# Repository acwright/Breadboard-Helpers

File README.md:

# Breadboard Helpers

A set of circuit boards to make breadboarding and prototyping easier!

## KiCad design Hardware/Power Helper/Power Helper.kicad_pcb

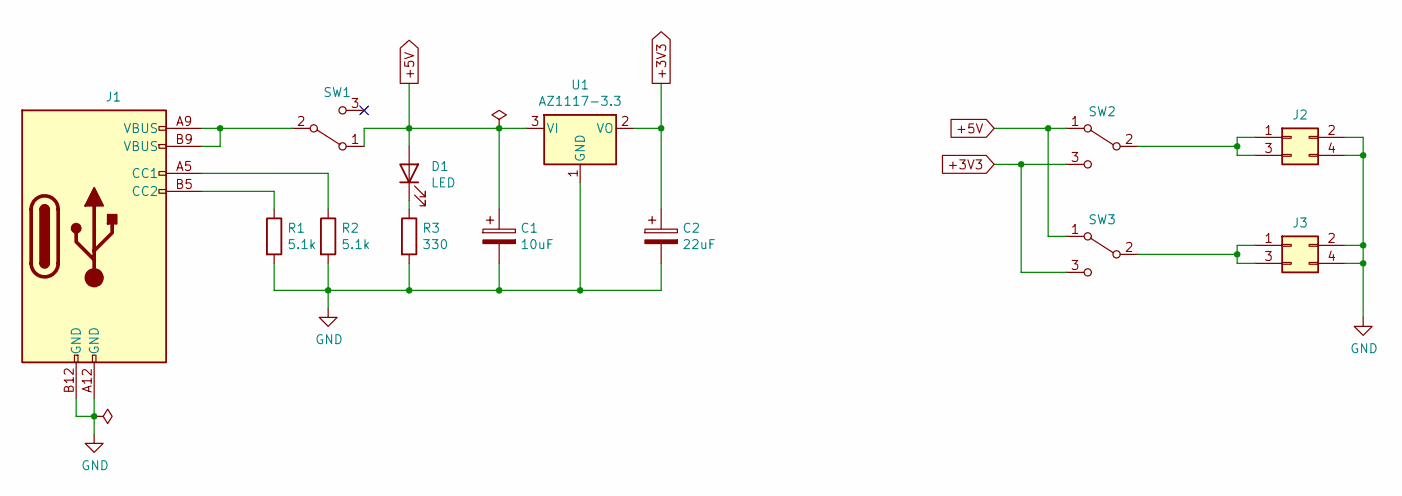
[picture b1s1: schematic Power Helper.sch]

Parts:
C1: 10uF; C_1206_3216Metric; LCSC C7171
C2: 22uF; C_1206_3216Metric; LCSC C129272
D1: LED; LED_0805_2012Metric; LCSC C2293
J1: USB_C_Receptacle_Power_Only; CUI_UJC-HP-3-SMT-TR; LCSC C283540
J2, J3: Conn_02x02_Odd_Even; PinHeader_2x02_P2.54mm_Vertical
R1, R2: 5.1k; R_0805_2012Metric; LCSC C27834
R3: 330; R_0805_2012Metric; LCSC C17630
SW1, SW2, SW3: SW_SPDT; SWITCH_SPST_SMD_A
U1: AZ1117-3.3; SOT-223-3_TabPin2; LCSC C108492

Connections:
+3V3: C2.1, SW2.3 (C), SW3.3 (C), U1.2 (VO)
+5V: C1.1, D1.2 (A), SW1.1 (A), SW2.1 (A), SW3.1 (A), U1.3 (VI)
GND: C1.2, C2.2, J1.A12 (GND), J1.B12 (GND), J2.2, J2.4, J3.2, J3.4, R1.2, R2.2, R3.2, U1.1 (GND)
unnamed: D1.1 (K), R3.1
unnamed: J1.A5 (CC1), R2.1
unnamed: J1.A9 (VBUS), J1.B9 (VBUS), SW1.2 (B)
unnamed: J1.B5 (CC2), R1.1
unnamed: J2.1, J2.3, SW2.2 (B)
unnamed: J3.1, J3.3, SW3.2 (B)

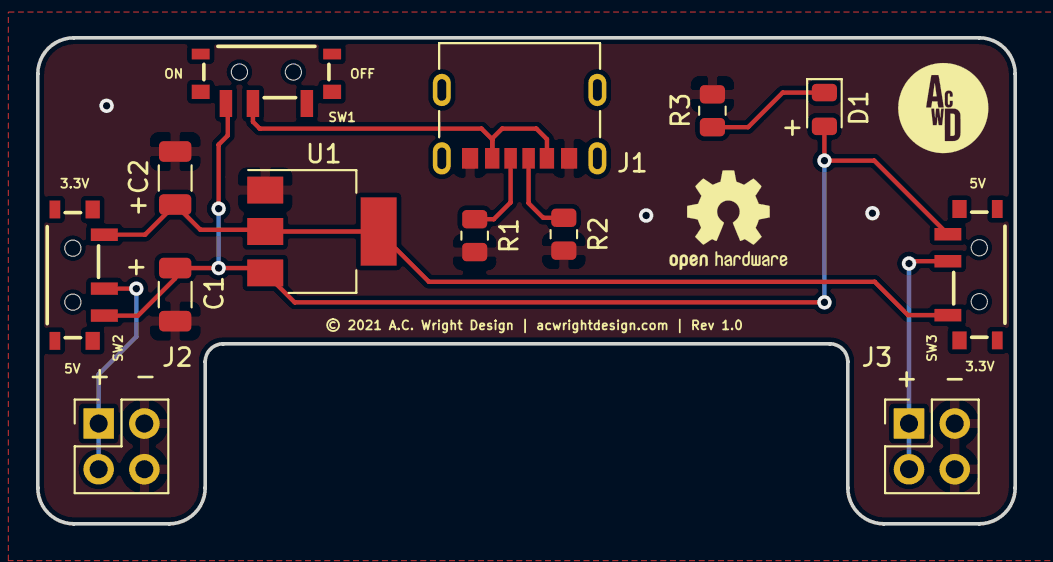
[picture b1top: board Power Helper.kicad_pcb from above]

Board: 2 copper layers, 54.3 x 27.0 mm, 13 parts (0 on the bottom side), 9 nets.

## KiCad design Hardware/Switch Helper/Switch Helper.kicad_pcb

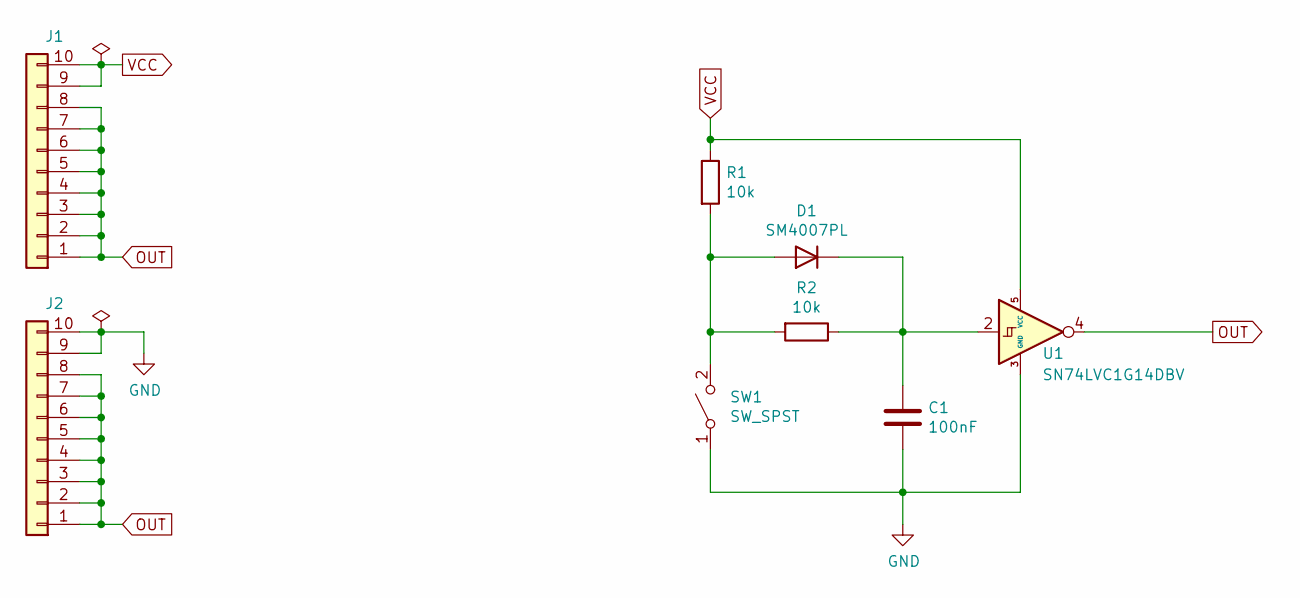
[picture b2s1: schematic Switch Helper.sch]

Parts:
C1: 100nF; C_0805_2012Metric; LCSC C49678
D1: SM4007PL; D_SOD-123F; LCSC C64898
J1, J2: Conn_01x10; PinHeader_1x10_P2.54mm_Vertical
R1, R2: 10k; R_0805_2012Metric; LCSC C17414
SW1: SW_SPST; SW_TS-1187A-B-A-B; LCSC C318884
U1: SN74LVC1G14DBV; SOT-23-5; LCSC C7835

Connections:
GND: C1.2, J2.9, J2.10, SW1.1 (A), U1.3 (GND)
unnamed: C1.1, D1.1 (K), R2.1, U1.2
unnamed: D1.2 (A), R1.2, R2.2, SW1.2 (B)
OUT: J1.1, J1.2, J1.3, J1.4, J1.5, J1.6, J1.7, J1.8, J2.1, J2.2, J2.3, J2.4, J2.5, J2.6, J2.7, J2.8, U1.4
VCC: J1.9, J1.10, R1.1, U1.5 (VCC)

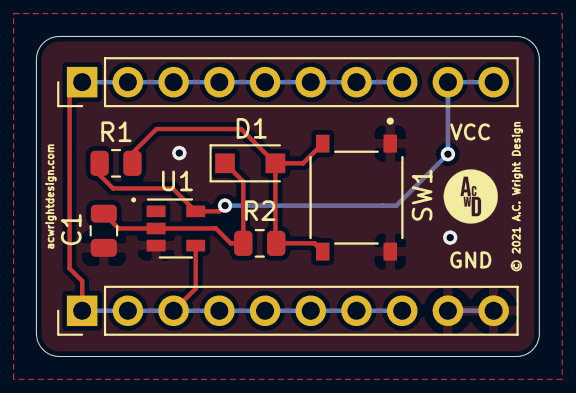
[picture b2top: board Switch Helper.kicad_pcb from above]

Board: 2 copper layers, 27.9 x 17.8 mm, 8 parts (0 on the bottom side), 5 nets.

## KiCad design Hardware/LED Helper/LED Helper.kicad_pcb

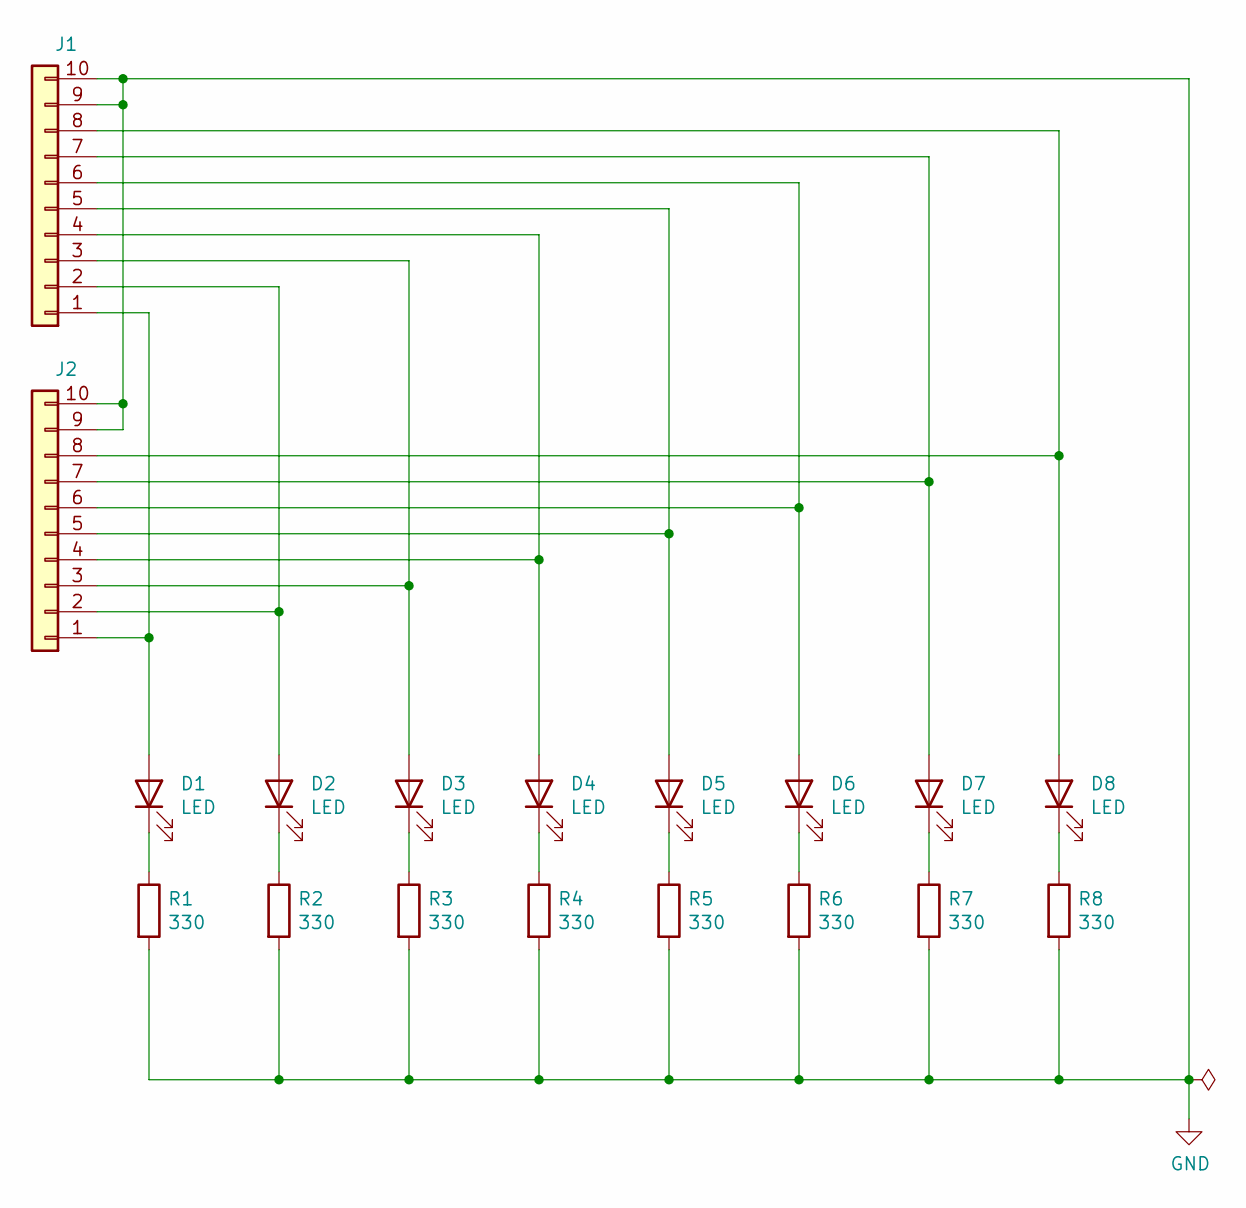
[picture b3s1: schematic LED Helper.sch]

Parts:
D1, D2, D3, D4, D5, D6, D7, D8: LED; LED_0805_2012Metric; LCSC C2293
J1, J2: Conn_01x10; PinHeader_1x10_P2.54mm_Vertical
R1, R2, R3, R4, R5, R6, R7, R8: 330; R_0805_2012Metric; LCSC C17630

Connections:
GND: J1.9, J1.10, J2.9, J2.10, R1.2, R2.2, R3.2, R4.2, R5.2, R6.2, R7.2, R8.2
unnamed: D1.1 (K), R1.1
unnamed: D1.2 (A), J1.1, J2.1
unnamed: D2.1 (K), R2.1
unnamed: D2.2 (A), J1.2, J2.2
unnamed: D3.1 (K), R3.1
unnamed: D3.2 (A), J1.3, J2.3
unnamed: D4.1 (K), R4.1
unnamed: D4.2 (A), J1.4, J2.4
unnamed: D5.1 (K), R5.1
unnamed: D5.2 (A), J1.5, J2.5
unnamed: D6.1 (K), R6.1
unnamed: D6.2 (A), J1.6, J2.6
unnamed: D7.1 (K), R7.1
unnamed: D7.2 (A), J1.7, J2.7
unnamed: D8.1 (K), R8.1
unnamed: D8.2 (A), J1.8, J2.8

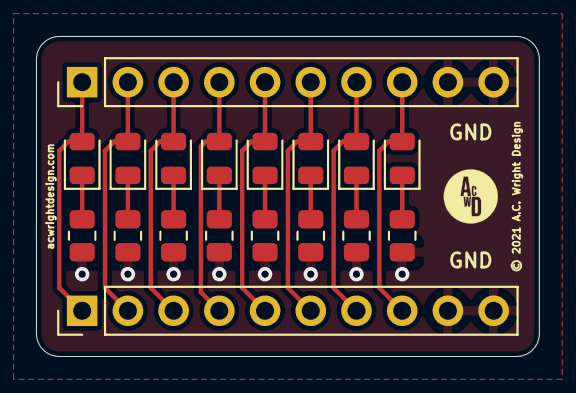
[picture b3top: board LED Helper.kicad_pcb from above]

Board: 2 copper layers, 27.9 x 17.8 mm, 18 parts (0 on the bottom side), 17 nets.

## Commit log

2021-04-02 JLC fix
2021-04-07 Add LED helper
2021-04-07 Add switch helper
2021-04-08 Cleanup
2021-04-09 Prepare for production

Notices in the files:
Hardware/LED Helper/LED Helper.kicad_pcb:
© 2021 A.C. Wright Design
Hardware/Power Helper/Power Helper.kicad_pcb:
© 2021 A.C. Wright Design | acwrightdesign.com | Rev 1.0
